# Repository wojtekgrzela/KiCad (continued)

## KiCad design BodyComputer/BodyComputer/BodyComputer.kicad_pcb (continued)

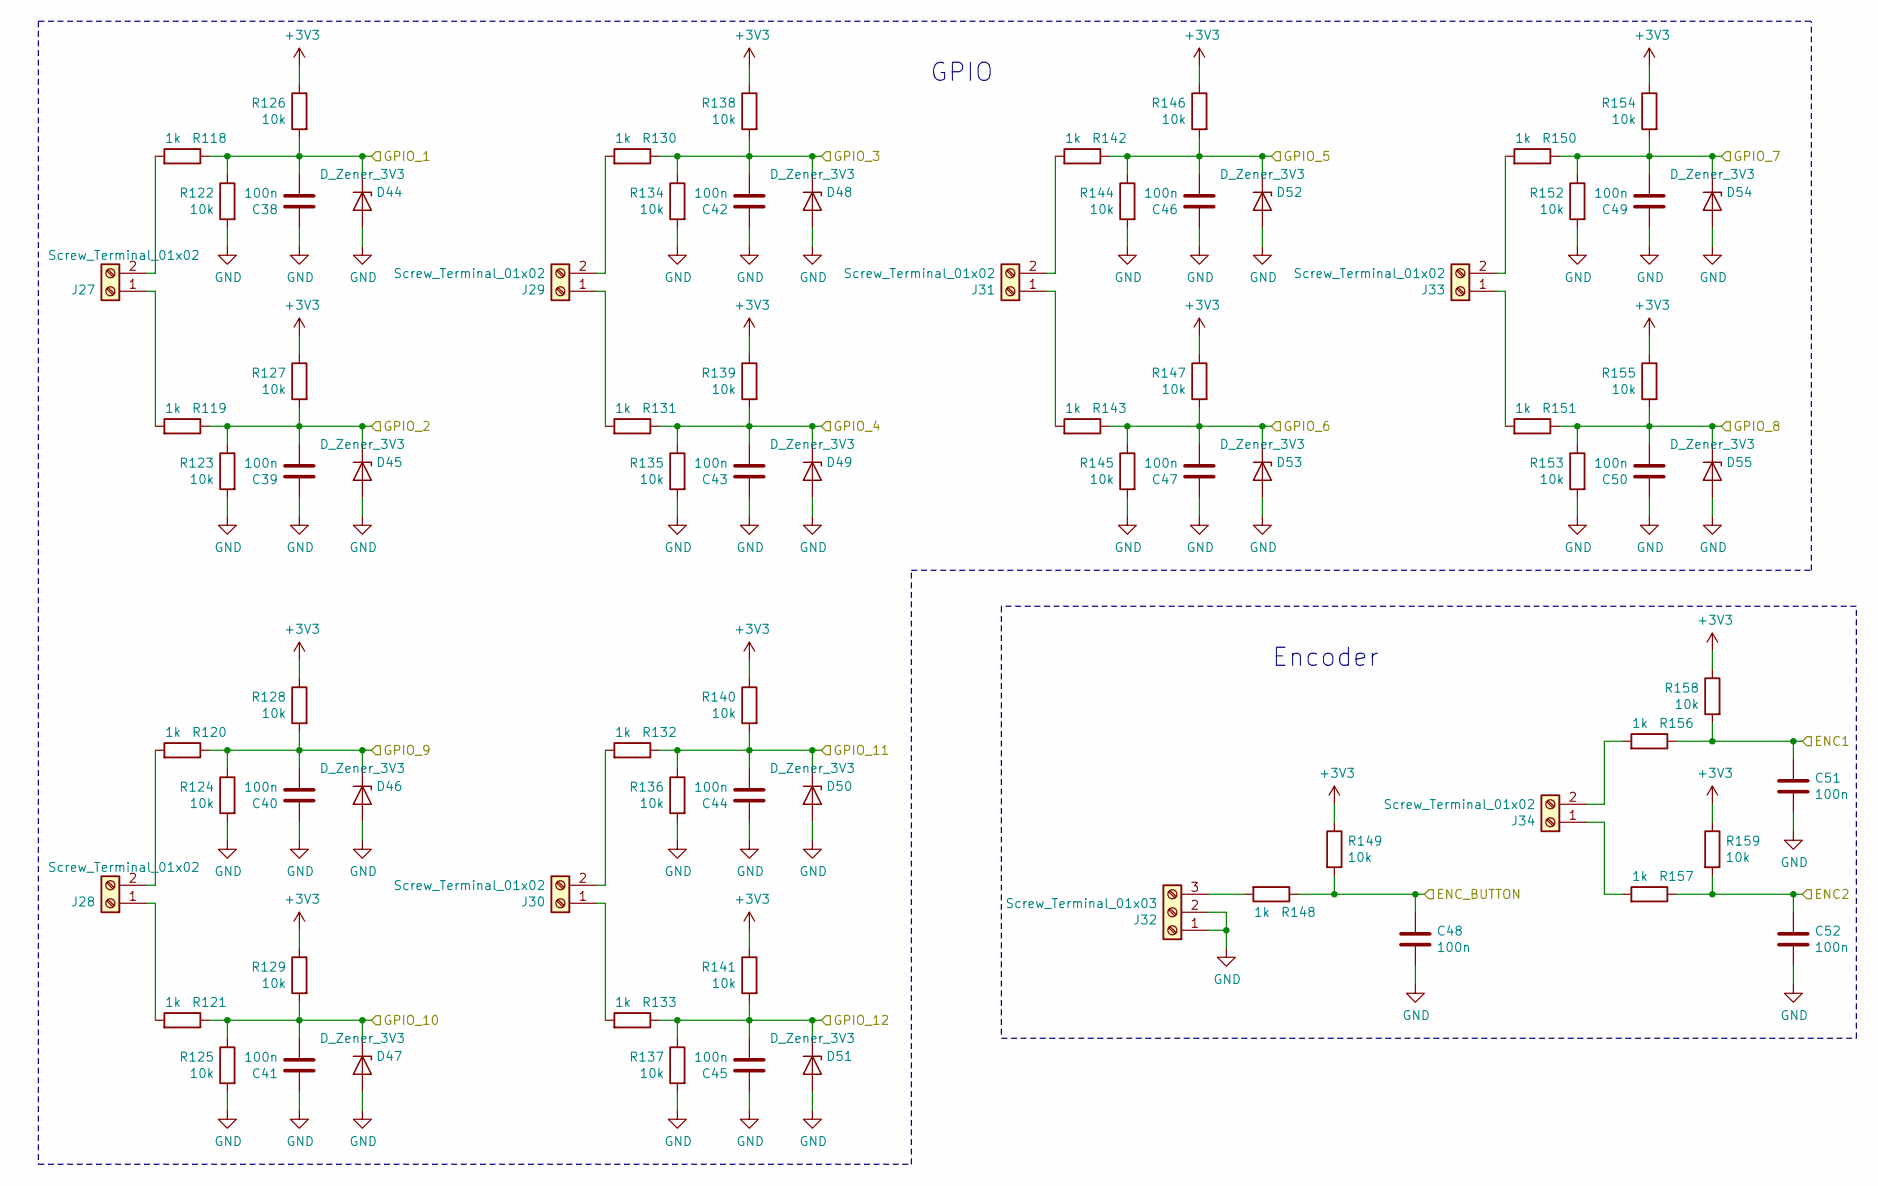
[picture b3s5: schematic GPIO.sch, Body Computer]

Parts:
C38, C39, C40, C41, C42, C43, C44, C45, C46, C47, C48, C49, C50, C51, C52: 100n; C_0603_1608Metric
D44, D45, D46, D47, D48, D49, D50, D51, D52, D53, D54, D55: D_Zener_3V3; D_SOD-323_HandSoldering
J27, J28, J29, J30, J31, J33, J34: Screw_Terminal_01x02; SHDR2W99P0X500_1X2_1000X760X1000P
J32: Screw_Terminal_01x03; SHDR3W95P0X500_1X3_1620X900X1280P
R118, R119, R120, R121, R130, R131, R132, R133, R142, R143, R148, R150, R151, R156, R157: 1k; R_0603_1608Metric
R122, R123, R124, R125, R126, R127, R128, R129, R134, R135, R136, R137, R138, R139, R140, R141, R144, R145, R146, R147, R149, R152, R153, R154, R155, R158, R159: 10k; R_0603_1608Metric

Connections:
+3V3: R126.1, R127.1, R128.1, R129.1, R138.1, R139.1, R140.1, R141.1, R146.1, R147.1, R149.1, R154.1, R155.1, R158.1, R159.1; also elsewhere on the board
/GPIO/ENC1: C51.1, R156.1, R158.2; also elsewhere on the board
/GPIO/ENC2: C52.1, R157.1, R159.2; also elsewhere on the board
/GPIO/ENC_BUTTON: C48.1, R148.1, R149.2; also elsewhere on the board
/GPIO/GPIO_1: C38.2, D44.1 (K), R118.1, R122.1, R126.2; also elsewhere on the board
/GPIO/GPIO_2: C39.2, D45.1 (K), R119.1, R123.1, R127.2; also elsewhere on the board
/GPIO/GPIO_3: C42.2, D48.1 (K), R130.1, R134.1, R138.2; also elsewhere on the board
/GPIO/GPIO_4: C43.2, D49.1 (K), R131.1, R135.1, R139.2; also elsewhere on the board
/GPIO/GPIO_5: C46.2, D52.1 (K), R142.1, R144.1, R146.2; also elsewhere on the board
/GPIO/GPIO_6: C47.2, D53.1 (K), R143.1, R145.1, R147.2; also elsewhere on the board
/GPIO/GPIO_7: C49.2, D54.1 (K), R150.1, R152.1, R154.2; also elsewhere on the board
/GPIO/GPIO_8: C50.2, D55.1 (K), R151.1, R153.1, R155.2; also elsewhere on the board
/GPIO/GPIO_9: C40.2, D46.1 (K), R120.1, R124.1, R128.2; also elsewhere on the board
/GPIO/GPIO_10: C41.2, D47.1 (K), R121.1, R125.1, R129.2; also elsewhere on the board
/GPIO/GPIO_11: C44.2, D50.1 (K), R132.1, R136.1, R140.2; also elsewhere on the board
/GPIO/GPIO_12: C45.2, D51.1 (K), R133.1, R137.1, R141.2; also elsewhere on the board
GND: C38.1, C39.1, C40.1, C41.1, C42.1, C43.1, C44.1, C45.1, C46.1, C47.1, C48.2, C49.1, C50.1, C51.2, C52.2, D44.2 (A), D45.2 (A), D46.2 (A), D47.2 (A), D48.2 (A), D49.2 (A), D50.2 (A), D51.2 (A), D52.2 (A), D53.2 (A), D54.2 (A), D55.2 (A), J32.1, J32.2, R122.2, R123.2, R124.2, R125.2, R134.2, R135.2, R136.2, R137.2, R144.2, R145.2, R152.2, R153.2; also elsewhere on the board
unnamed: J27.1, R119.2
unnamed: J27.2, R118.2
unnamed: J28.1, R121.2
unnamed: J28.2, R120.2
unnamed: J29.1, R131.2
unnamed: J29.2, R130.2
unnamed: J30.1, R133.2
unnamed: J30.2, R132.2
unnamed: J31.1, R143.2
unnamed: J31.2, R142.2
unnamed: J32.3, R148.2
unnamed: J33.1, R151.2
unnamed: J33.2, R150.2
unnamed: J34.1, R157.2
unnamed: J34.2, R156.2

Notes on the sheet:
GPIO
Encoder

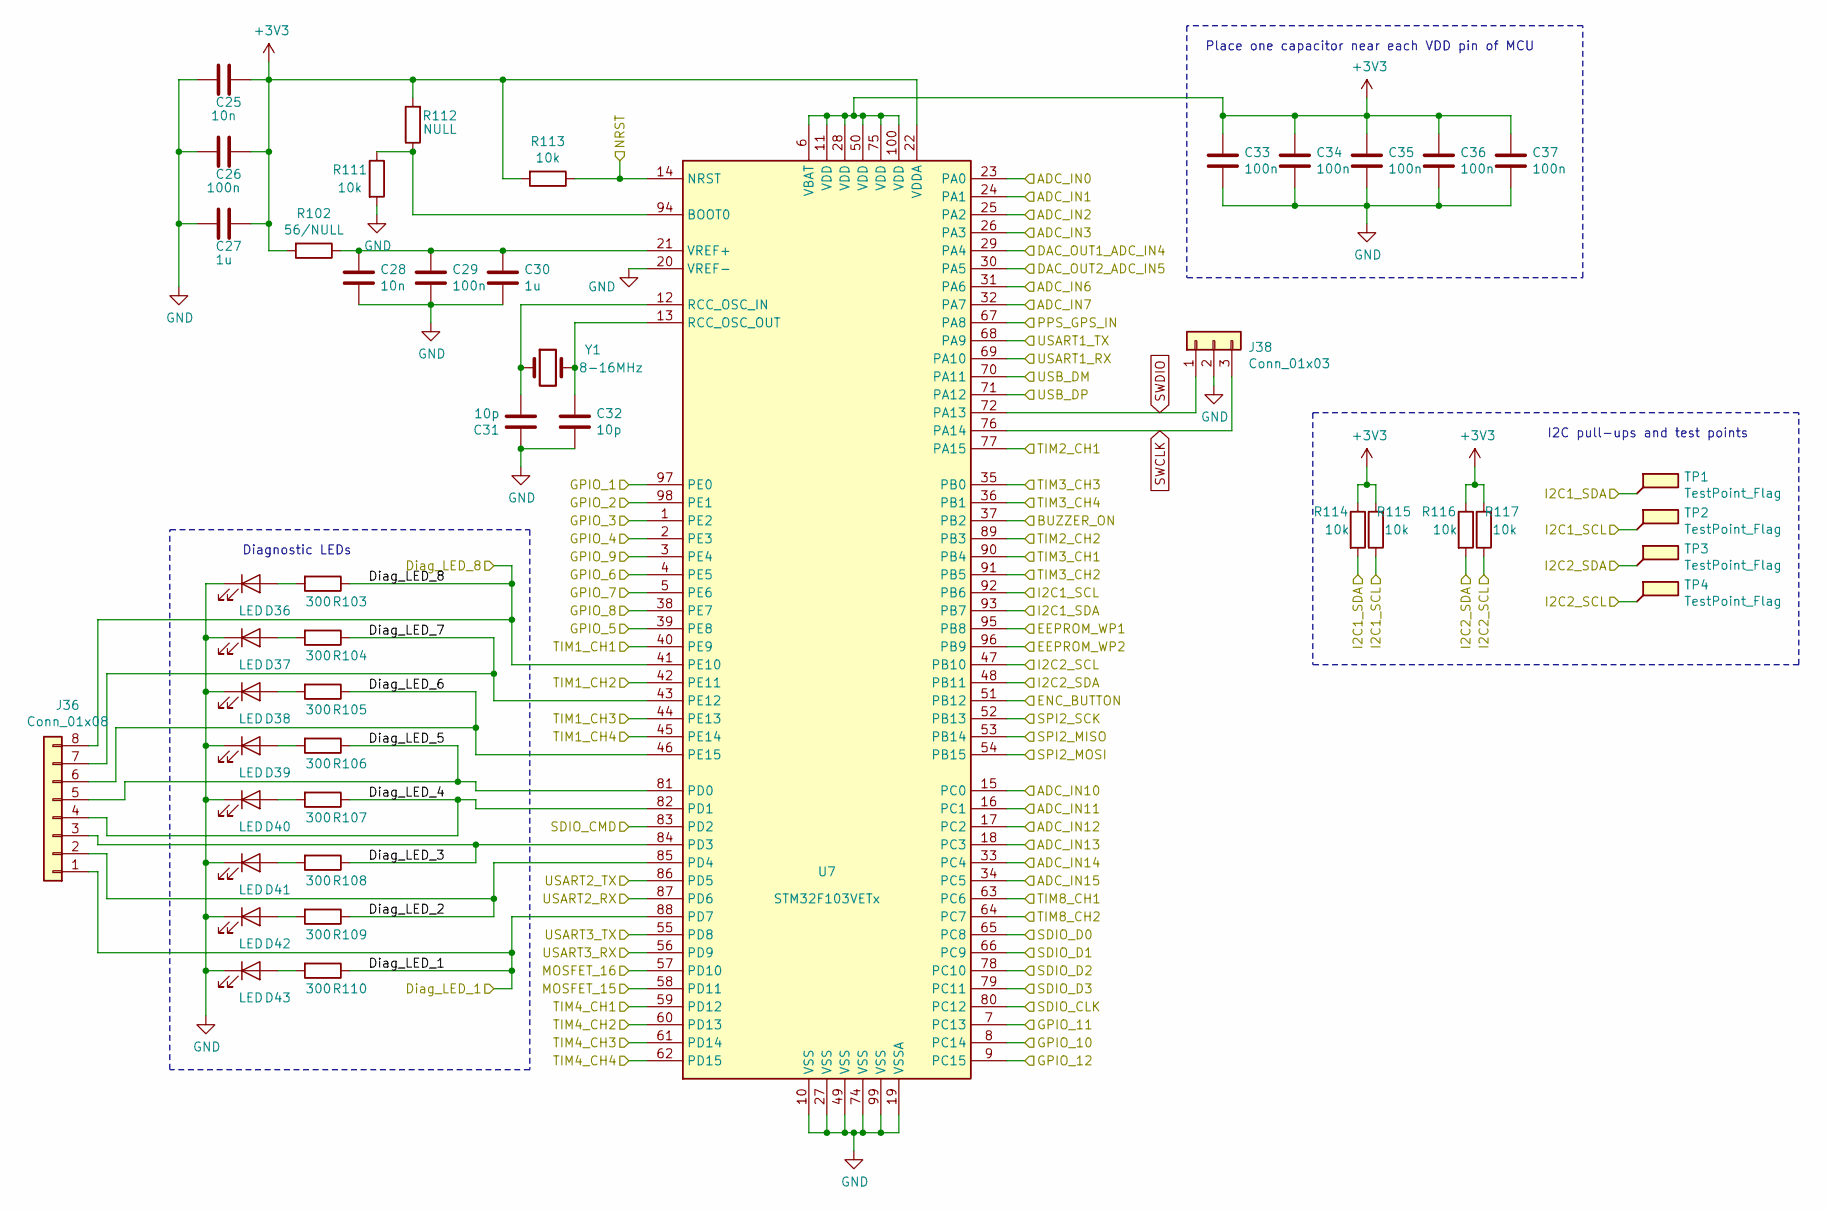
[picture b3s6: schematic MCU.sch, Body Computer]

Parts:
C25, C28: 10n; C_0603_1608Metric
C26, C29, C33, C34, C35, C36, C37: 100n; C_0603_1608Metric
C27, C30: 1u; C_0603_1608Metric
C31, C32: 10p; C_0603_1608Metric
D36, D37, D38, D39, D40, D41, D42, D43: LED; D_0603_1608Metric_Pad1.05x0.95mm_HandSolder
J36: Conn_01x08; PinHeader_1x08_P2.54mm_Vertical
J38: Conn_01x03; PinHeader_1x03_P2.54mm_Vertical
R102: 56/NULL; R_0603_1608Metric
R103, R104, R105, R106, R107, R108, R109, R110: 300; R_0603_1608Metric
R111, R113, R114, R115, R116, R117: 10k; R_0603_1608Metric
R112: NULL; R_0603_1608Metric
TP1, TP2, TP3, TP4: TestPoint_Flag; TestPoint_Pad_D1.0mm
U7: STM32F103VETx; LQFP-100_14x14mm_P0.5mm
Y1: 8-16MHz; Crystal_SMD_SeikoEpson_MA505-2Pin_12.7x5.1mm

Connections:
+3V3: C25.1, C26.1, C27.1, C33.1, C34.1, C35.1, C36.1, C37.1, R102.2, R112.2, R113.2, R114.1, R115.2, R116.1, R117.2, U7.6 (VBAT), U7.11 (VDD), U7.22 (VDDA), U7.28 (VDD), U7.50 (VDD), U7.75 (VDD), U7.100 (VDD); also elsewhere on the board
/GPIO/ENC1: U7.63 (PC6); also elsewhere on the board
/GPIO/ENC2: U7.64 (PC7); also elsewhere on the board
/GPIO/ENC_BUTTON: U7.51 (PB12); also elsewhere on the board
/GPIO/GPIO_1: U7.97 (PE0); also elsewhere on the board
/GPIO/GPIO_2: U7.98 (PE1); also elsewhere on the board
/GPIO/GPIO_3: U7.1 (PE2); also elsewhere on the board
/GPIO/GPIO_4: U7.2 (PE3); also elsewhere on the board
/GPIO/GPIO_5: U7.39 (PE8); also elsewhere on the board
/GPIO/GPIO_6: U7.4 (PE5); also elsewhere on the board
/GPIO/GPIO_7: U7.5 (PE6); also elsewhere on the board
/GPIO/GPIO_8: U7.38 (PE7); also elsewhere on the board
/GPIO/GPIO_9: U7.3 (PE4); also elsewhere on the board
/GPIO/GPIO_10: U7.8 (PC14); also elsewhere on the board
/GPIO/GPIO_11: U7.7 (PC13); also elsewhere on the board
/GPIO/GPIO_12: U7.9 (PC15); also elsewhere on the board
/Inputs_Outputs/ADC_1: U7.25 (PA2); also elsewhere on the board
/Inputs_Outputs/ADC_2: U7.26 (PA3); also elsewhere on the board
/Inputs_Outputs/ADC_3: U7.31 (PA6); also elsewhere on the board
/Inputs_Outputs/ADC_4: U7.32 (PA7); also elsewhere on the board
/Inputs_Outputs/ADC_5: U7.33 (PC4); also elsewhere on the board
/Inputs_Outputs/ADC_6: U7.34 (PC5); also elsewhere on the board
/Inputs_Outputs/ADC_7: U7.23 (PA0); also elsewhere on the board
/Inputs_Outputs/ADC_8: U7.24 (PA1); also elsewhere on the board
/Inputs_Outputs/AN_IN1_DAC1_INPUT: U7.29 (PA4); also elsewhere on the board
/Inputs_Outputs/AN_IN2_DAC2_INPUT: U7.30 (PA5); also elsewhere on the board
/Inputs_Outputs/MOSFET_OUT_1: U7.40 (PE9); also elsewhere on the board
/Inputs_Outputs/MOSFET_OUT_2: U7.42 (PE11); also elsewhere on the board
/Inputs_Outputs/MOSFET_OUT_3: U7.44 (PE13); also elsewhere on the board
/Inputs_Outputs/MOSFET_OUT_4: U7.45 (PE14); also elsewhere on the board
/Inputs_Outputs/MOSFET_OUT_5: U7.77 (PA15); also elsewhere on the board
/Inputs_Outputs/MOSFET_OUT_6: U7.89 (PB3); also elsewhere on the board
/Inputs_Outputs/MOSFET_OUT_7: U7.90 (PB4); also elsewhere on the board
/Inputs_Outputs/MOSFET_OUT_8: U7.91 (PB5); also elsewhere on the board
/Inputs_Outputs/MOSFET_OUT_9: U7.35 (PB0); also elsewhere on the board
/Inputs_Outputs/MOSFET_OUT_10: U7.36 (PB1); also elsewhere on the board
/Inputs_Outputs/MOSFET_OUT_11: U7.59 (PD12); also elsewhere on the board
/Inputs_Outputs/MOSFET_OUT_12: U7.60 (PD13); also elsewhere on the board
/Inputs_Outputs/MOSFET_OUT_13: U7.61 (PD14); also elsewhere on the board
/Inputs_Outputs/MOSFET_OUT_14: U7.62 (PD15); also elsewhere on the board
/MCU/ADC_IN10: U7.15 (PC0); also elsewhere on the board
/MCU/ADC_IN12: U7.17 (PC2); also elsewhere on the board
/MCU/ADC_IN13: U7.18 (PC3); also elsewhere on the board
/MCU/Diag_LED_1: J36.1, R110.1, U7.88 (PD7); also elsewhere on the board
/MCU/Diag_LED_2: J36.2, R109.1, U7.85 (PD4)
/MCU/Diag_LED_3: J36.3, R108.1, U7.84 (PD3)
/MCU/Diag_LED_4: J36.4, R107.1, U7.82 (PD1)
/MCU/Diag_LED_5: J36.5, R106.1, U7.81 (PD0)
/MCU/Diag_LED_6: J36.6, R105.1, U7.46 (PE15)
/MCU/Diag_LED_7: J36.7, R104.1, U7.43 (PE12)
/MCU/Diag_LED_8: J36.8, R103.1, U7.41 (PE10); also elsewhere on the board
/MCU/EEPROM_WP1: U7.95 (PB8); also elsewhere on the board
/MCU/EEPROM_WP2: U7.96 (PB9); also elsewhere on the board
/MCU/I2C2_SCL: R117.1, TP4.1, U7.47 (PB10); also elsewhere on the board
/MCU/I2C2_SDA: R116.2, TP3.1, U7.48 (PB11); also elsewhere on the board
/MCU/MOSFET_15: U7.58 (PD11); also elsewhere on the board
/MCU/MOSFET_16: U7.57 (PD10); also elsewhere on the board
/MCU/NRST: R113.1, U7.14 (NRST); also elsewhere on the board
/Memory/EEPROM_SCL: R115.1, TP2.1, U7.92 (PB6); also elsewhere on the board
/Memory/EEPROM_SDA: R114.2, TP1.1, U7.93 (PB7); also elsewhere on the board
/Memory/FLASH_DATA_0: U7.65 (PC8); also elsewhere on the board
/Memory/FLASH_DATA_1: U7.66 (PC9); also elsewhere on the board
/Memory/FLASH_DATA_2: U7.78 (PC10); also elsewhere on the board
/Memory/FLASH_DATA_3: U7.79 (PC11); also elsewhere on the board
/Memory/FLASH_DATA_CLK: U7.80 (PC12); also elsewhere on the board
/Memory/FLASH_DATA_CMD: U7.83 (PD2); also elsewhere on the board
/Peripherals/BUZZER: U7.37 (PB2); also elsewhere on the board
/Peripherals/MISO: U7.53 (PB14); also elsewhere on the board
/Peripherals/MOSI: U7.54 (PB15); also elsewhere on the board
/Peripherals/PPS_GPS: U7.67 (PA8); also elsewhere on the board
/Peripherals/RX: U7.56 (PD9); also elsewhere on the board
/Peripherals/RXD2_NODEMCU: U7.86 (PD5); also elsewhere on the board
/Peripherals/RX_GPS: U7.68 (PA9); also elsewhere on the board
/Peripherals/SCK: U7.52 (PB13); also elsewhere on the board
/Peripherals/TX: U7.55 (PD8); also elsewhere on the board
/Peripherals/TX2D_NODEMCU: U7.87 (PD6); also elsewhere on the board
/Peripherals/TX_GPS: U7.69 (PA10); also elsewhere on the board
/Peripherals/USB_DATA+: U7.71 (PA12); also elsewhere on the board
/Peripherals/USB_DATA-: U7.70 (PA11); also elsewhere on the board
/PowerSupply_and_BoardTemp/5V_MEASURE: U7.16 (PC1); also elsewhere on the board
GND: C25.2, C26.2, C27.2, C28.2, C29.2, C30.2, C31.1, C32.2, C33.2, C34.2, C35.2, C36.2, C37.2, D36.1 (K), D37.1 (K), D38.1 (K), D39.1 (K), D40.1 (K), D41.1 (K), D42.1 (K), D43.1 (K), J38.2, R111.2, U7.10 (VSS), U7.19 (VSSA), U7.20 (VREF-), U7.27 (VSS), U7.49 (VSS), U7.74 (VSS), U7.99 (VSS); also elsewhere on the board
unnamed: C28.1, C29.1, C30.1, R102.1, U7.21 (VREF+)
unnamed: C31.2, U7.12 (RCC_OSC_IN), Y1.1
unnamed: C32.1, U7.13 (RCC_OSC_OUT), Y1.2
unnamed: D36.2 (A), R103.2
unnamed: D37.2 (A), R104.2
unnamed: D38.2 (A), R105.2
unnamed: D39.2 (A), R106.2
unnamed: D40.2 (A), R107.2
unnamed: D41.2 (A), R108.2
unnamed: D42.2 (A), R109.2
unnamed: D43.2 (A), R110.2
unnamed: R111.1, R112.1, U7.94 (BOOT0)
SWCLK: J38.3, U7.76 (PA14)
SWDIO: J38.1, U7.72 (PA13)

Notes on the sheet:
Place one capacitor near each VDD pin of MCU
I2C pull-ups and test points
Diagnostic LEDs

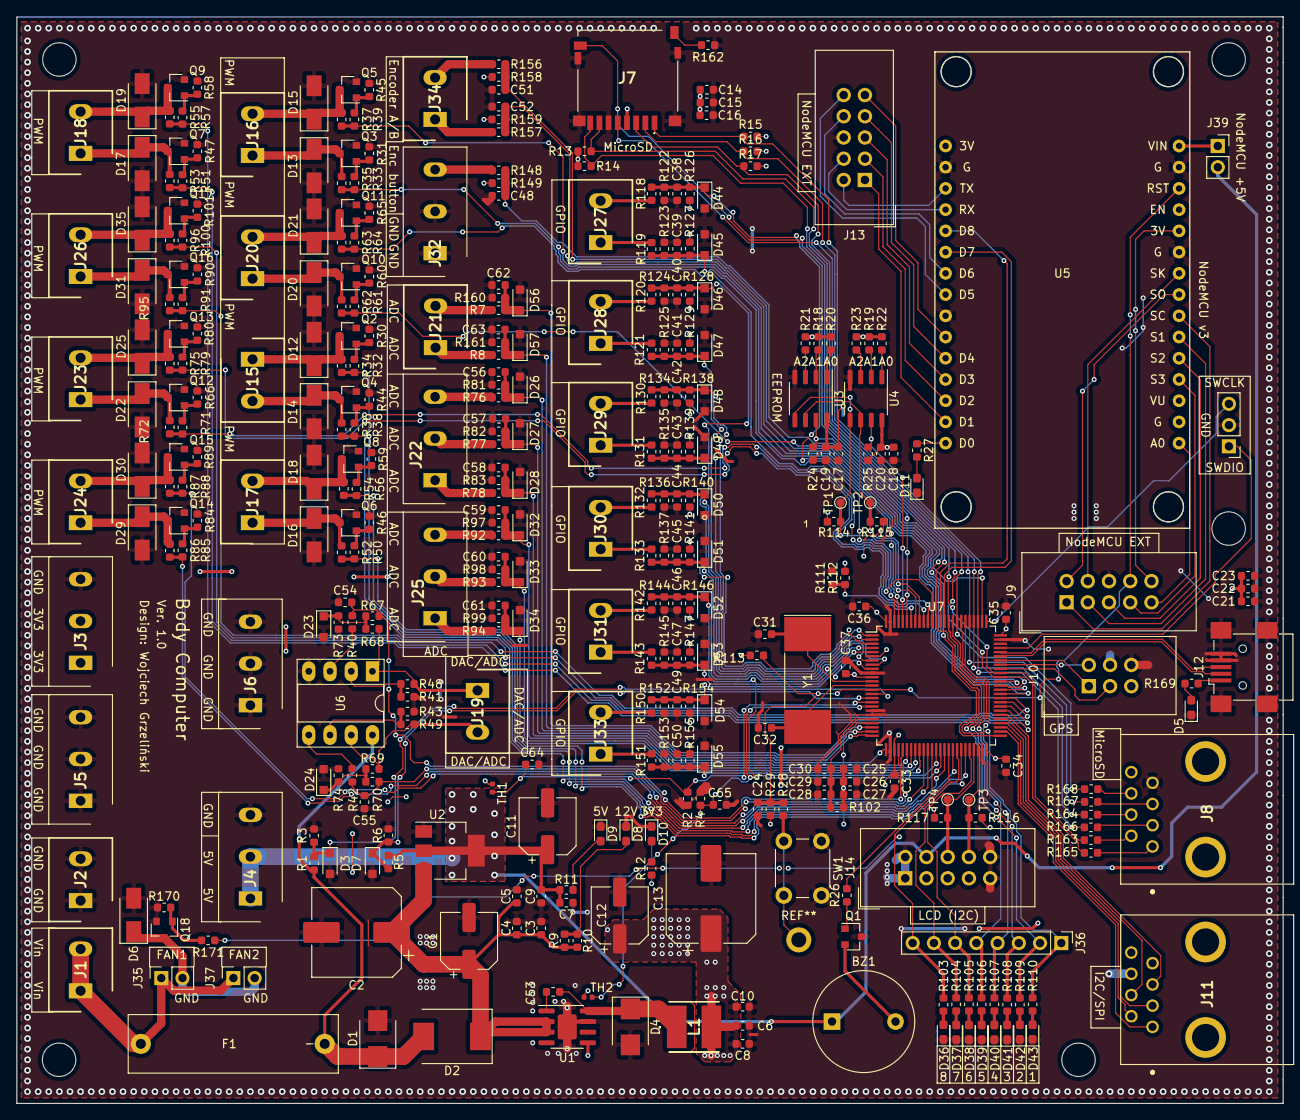
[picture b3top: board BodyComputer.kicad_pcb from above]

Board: 2 copper layers, 151.5 x 130.0 mm, 368 parts (0 on the bottom side), 207 nets.

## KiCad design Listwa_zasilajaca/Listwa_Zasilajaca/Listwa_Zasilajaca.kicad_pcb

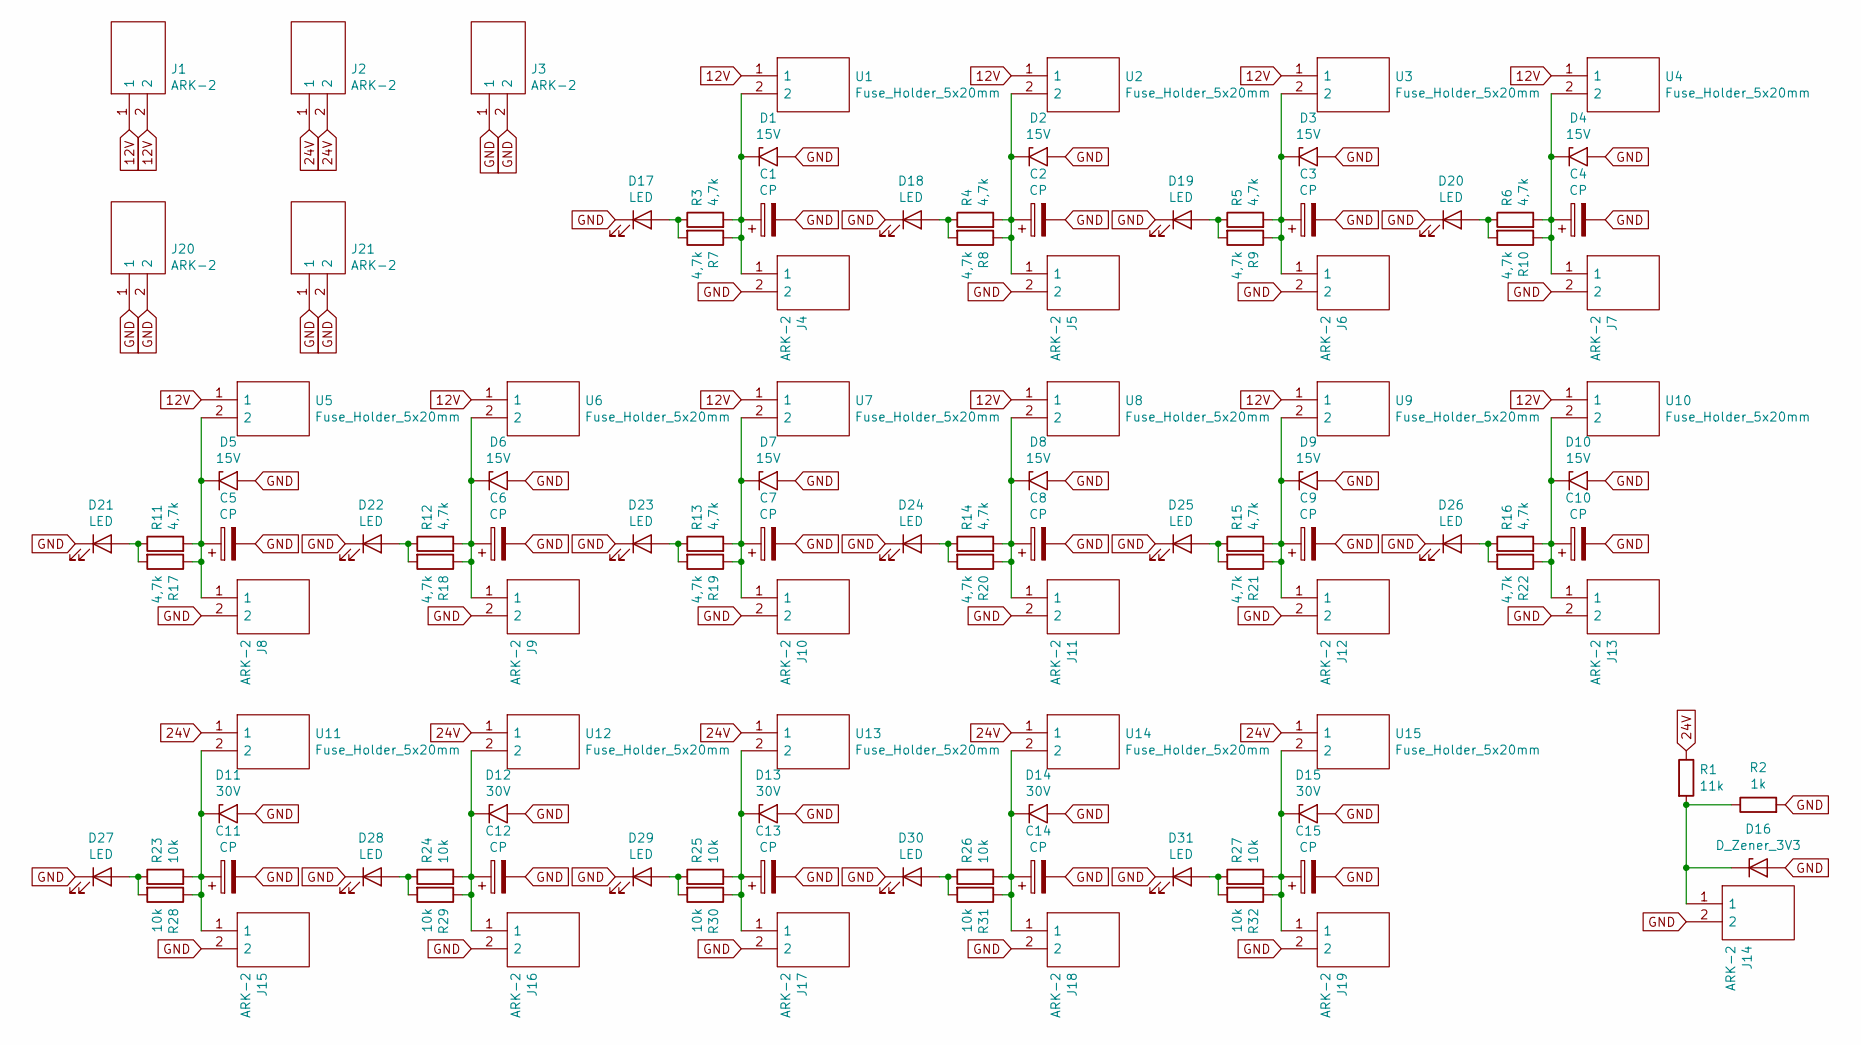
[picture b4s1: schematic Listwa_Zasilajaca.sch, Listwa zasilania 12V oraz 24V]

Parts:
C1, C2, C3, C4, C5, C6, C7, C8, C9, C10, C11, C12, C13, C14, C15: CP; CP_Radial_D5.0mm_P2.00mm
D1, D2, D3, D4, D5, D6, D7, D8, D9, D10: 15V; D_DO-201AE_P15.24mm_Horizontal
D11, D12, D13, D14, D15: 30V; D_DO-201AE_P15.24mm_Horizontal
D16: D_Zener_3V3; D_SOD-123
D17, D18, D19, D20, D21, D22, D23, D24, D25, D26, D27, D28, D29, D30, D31: LED; D_0603_1608Metric
J1, J2, J3, J4, J5, J6, J7, J8, J9, J10, J11, J12, J13, J14, J15, J16, J17, J18, J19, J20, J21: ARK-2; SHDR2W99P0X500_1X2_1000X760X1000P; Mouser Part Number 534-8718
R1: 11k; R_0603_1608Metric
R2: 1k; R_0603_1608Metric
R3, R4, R5, R6, R7, R8, R9, R10, R11, R12, R13, R14, R15, R16, R17, R18, R19, R20, R21, R22: 4,7k; R_0603_1608Metric
R23, R24, R25, R26, R27, R28, R29, R30, R31, R32: 10k; R_0603_1608Metric
U1, U2, U3, U4, U5, U6, U7, U8, U9, U10, U11, U12, U13, U14, U15: Fuse_Holder_5x20mm; 0PTF0078P; Mouser Part Number 576-0PTF0078P

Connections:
12V: J1.1, J1.2, U1.1, U2.1, U3.1, U4.1, U5.1, U6.1, U7.1, U8.1, U9.1, U10.1
24V: J2.1, J2.2, R1.1, U11.1, U12.1, U13.1, U14.1, U15.1
GND: C1.2, C2.2, C3.2, C4.2, C5.2, C6.2, C7.2, C8.2, C9.2, C10.2, C11.2, C12.2, C13.2, C14.2, C15.2, D1.2 (A2), D2.2 (A2), D3.2 (A2), D4.2 (A2), D5.2 (A2), D6.2 (A2), D7.2 (A2), D8.2 (A2), D9.2 (A2), D10.2 (A2), D11.2 (A2), D12.2 (A2), D13.2 (A2), D14.2 (A2), D15.2 (A2), D16.2 (A), D17.1 (K), D18.1 (K), D19.1 (K), D20.1 (K), D21.1 (K), D22.1 (K), D23.1 (K), D24.1 (K), D25.1 (K), D26.1 (K), D27.1 (K), D28.1 (K), D29.1 (K), D30.1 (K), D31.1 (K), J3.1, J3.2, J4.2, J5.2, J6.2, J7.2, J8.2, J9.2, J10.2, J11.2, J12.2, J13.2, J14.2, J15.2, J16.2, J17.2, J18.2, J19.2, J20.1, J20.2, J21.1, J21.2, R2.2
unnamed: C1.1, D1.1 (A1), J4.1, R3.2, R7.1, U1.2
unnamed: C2.1, D2.1 (A1), J5.1, R4.2, R8.1, U2.2
unnamed: C3.1, D3.1 (A1), J6.1, R5.2, R9.1, U3.2
unnamed: C4.1, D4.1 (A1), J7.1, R6.2, R10.1, U4.2
unnamed: C5.1, D5.1 (A1), J8.1, R11.2, R17.1, U5.2
unnamed: C6.1, D6.1 (A1), J9.1, R12.2, R18.1, U6.2
unnamed: C7.1, D7.1 (A1), J10.1, R13.2, R19.1, U7.2
unnamed: C8.1, D8.1 (A1), J11.1, R14.2, R20.1, U8.2
unnamed: C9.1, D9.1 (A1), J12.1, R15.2, R21.1, U9.2
unnamed: C10.1, D10.1 (A1), J13.1, R16.2, R22.1, U10.2
unnamed: C11.1, D11.1 (A1), J15.1, R23.2, R28.1, U11.2
unnamed: C12.1, D12.1 (A1), J16.1, R24.2, R29.1, U12.2
unnamed: C13.1, D13.1 (A1), J17.1, R25.2, R30.1, U13.2
unnamed: C14.1, D14.1 (A1), J18.1, R26.2, R31.1, U14.2
unnamed: C15.1, D15.1 (A1), J19.1, R27.2, R32.1, U15.2
unnamed: D16.1 (K), J14.1, R1.2, R2.1
unnamed: D17.2 (A), R3.1, R7.2
unnamed: D18.2 (A), R4.1, R8.2
unnamed: D19.2 (A), R5.1, R9.2
unnamed: D20.2 (A), R6.1, R10.2
unnamed: D21.2 (A), R11.1, R17.2
unnamed: D22.2 (A), R12.1, R18.2
unnamed: D23.2 (A), R13.1, R19.2
unnamed: D24.2 (A), R14.1, R20.2
unnamed: D25.2 (A), R15.1, R21.2
unnamed: D26.2 (A), R16.1, R22.2
unnamed: D27.2 (A), R23.1, R28.2
unnamed: D28.2 (A), R24.1, R29.2
unnamed: D29.2 (A), R25.1, R30.2
unnamed: D30.2 (A), R26.1, R31.2
unnamed: D31.2 (A), R27.1, R32.2

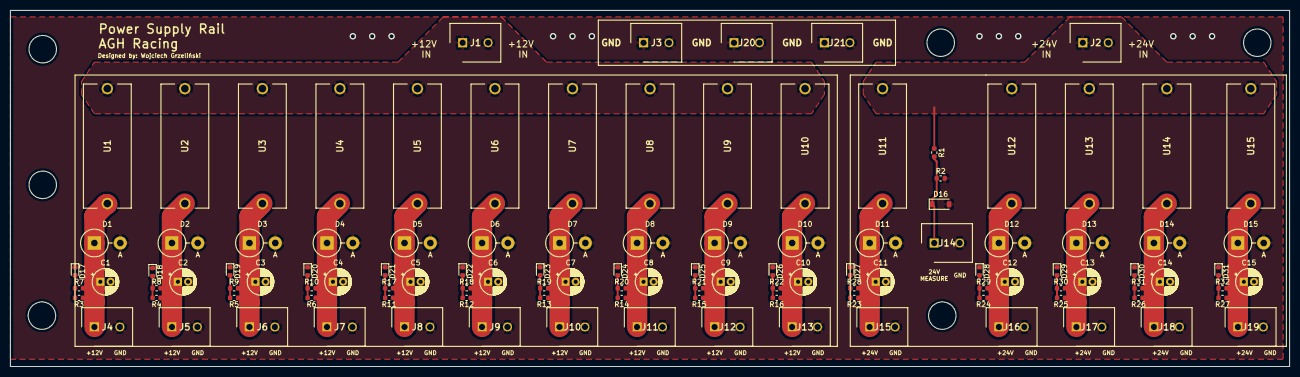
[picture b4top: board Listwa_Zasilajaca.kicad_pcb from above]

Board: 2 copper layers, 251.5 x 70.0 mm, 114 parts (0 on the bottom side), 34 nets.

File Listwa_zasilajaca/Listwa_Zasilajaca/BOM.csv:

Id,Oznaczenie,Obudowa,Ilość,Oznaczenie,Dostawca i numer artykułu
1,"J21,J20,J19,J18,J17,J16,J15,J14,J13,J12,J11,J10,J9,J8,J7,J6,J5,J4,J3,J2,J1",SHDR2W99P0X500_1X2_1000X760X1000P,21,ARK-2,https://www.tme.eu/pl/details/tb-5.0-p-2p-11/listwy-zaciskow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
2,"D15,D14,D13,D12,D11",D_DO-201_P5.08mm_Vertical_AnodeUp,5,30V,https://www.tme.eu/pl/details/1.5ke30a/diody-transil-tht-jed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
3,"D10,D9,D8,D7,D6,D5,D4,D3,D2,D1",D_DO-201_P5.08mm_Vertical_AnodeUp,10,15V,https://www.tme.eu/pl/details/1.5ke15a/diody-transil-tht-jed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
4,"U15,U14,U13,U12,U11,U10,U9,U8,U7,U6,U5,U4,U3,U2,U1",0PTF0078P,15,Fuse_Holder_5x20mm,https://www.tme.eu/pl/details/zhl78/gniazda-bezpiecznikowe-p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
5,R2,R_0603_1608Metric,1,1k,https://www.tme.eu/pl/details/wf06p-1k-5%25/rezystory-smd-06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
6,R1,R_0603_1608Metric,1,11k,https://www.tme.eu/pl/details/smd0603-11k/rezystory-smd-0603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
7,D16,D_SOD-123,1,D_Zener_3V3,https://www.tme.eu/pl/details/bzt52c3v3-7-f/diody-zenera-smd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
8,"C15,C14,C13,C12,C11,C10,C9,C8,C7,C6,C5,C4,C3,C2,C1",CP_Radial_D5.0mm_P2.00mm,15,CP,https://www.tme.eu/pl/details/pf1v330mnn0511u/kondensatory-e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
9,"R32,R31,R30,R29,R28,R27,R26,R25,R24,R23",R_0603_1608Metric,10,10k,https://www.tme.eu/pl/details/smd0603-10k/rezystory-smd-0603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 
10,"R22,R21,R20,R19,R18,R17,R16,R15,R14,R13,R12,R11,R10,R9,R8,R7,R6,R5,R4,R3",R_0603_1608Metric,20,"4,7k",https://www.tme.eu/pl/details/wf06p-4k7-5%25/rezystory-smd-0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 
11,"D31,D30,D29,D28,D27,D26,D25,D24,D23,D22,D21,D20,D19,D18,D17",D_0603_1608Metric,15,LED,https://www.tme.eu/pl/details/ll-s194pvc-v1-2b/diody-led-smd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

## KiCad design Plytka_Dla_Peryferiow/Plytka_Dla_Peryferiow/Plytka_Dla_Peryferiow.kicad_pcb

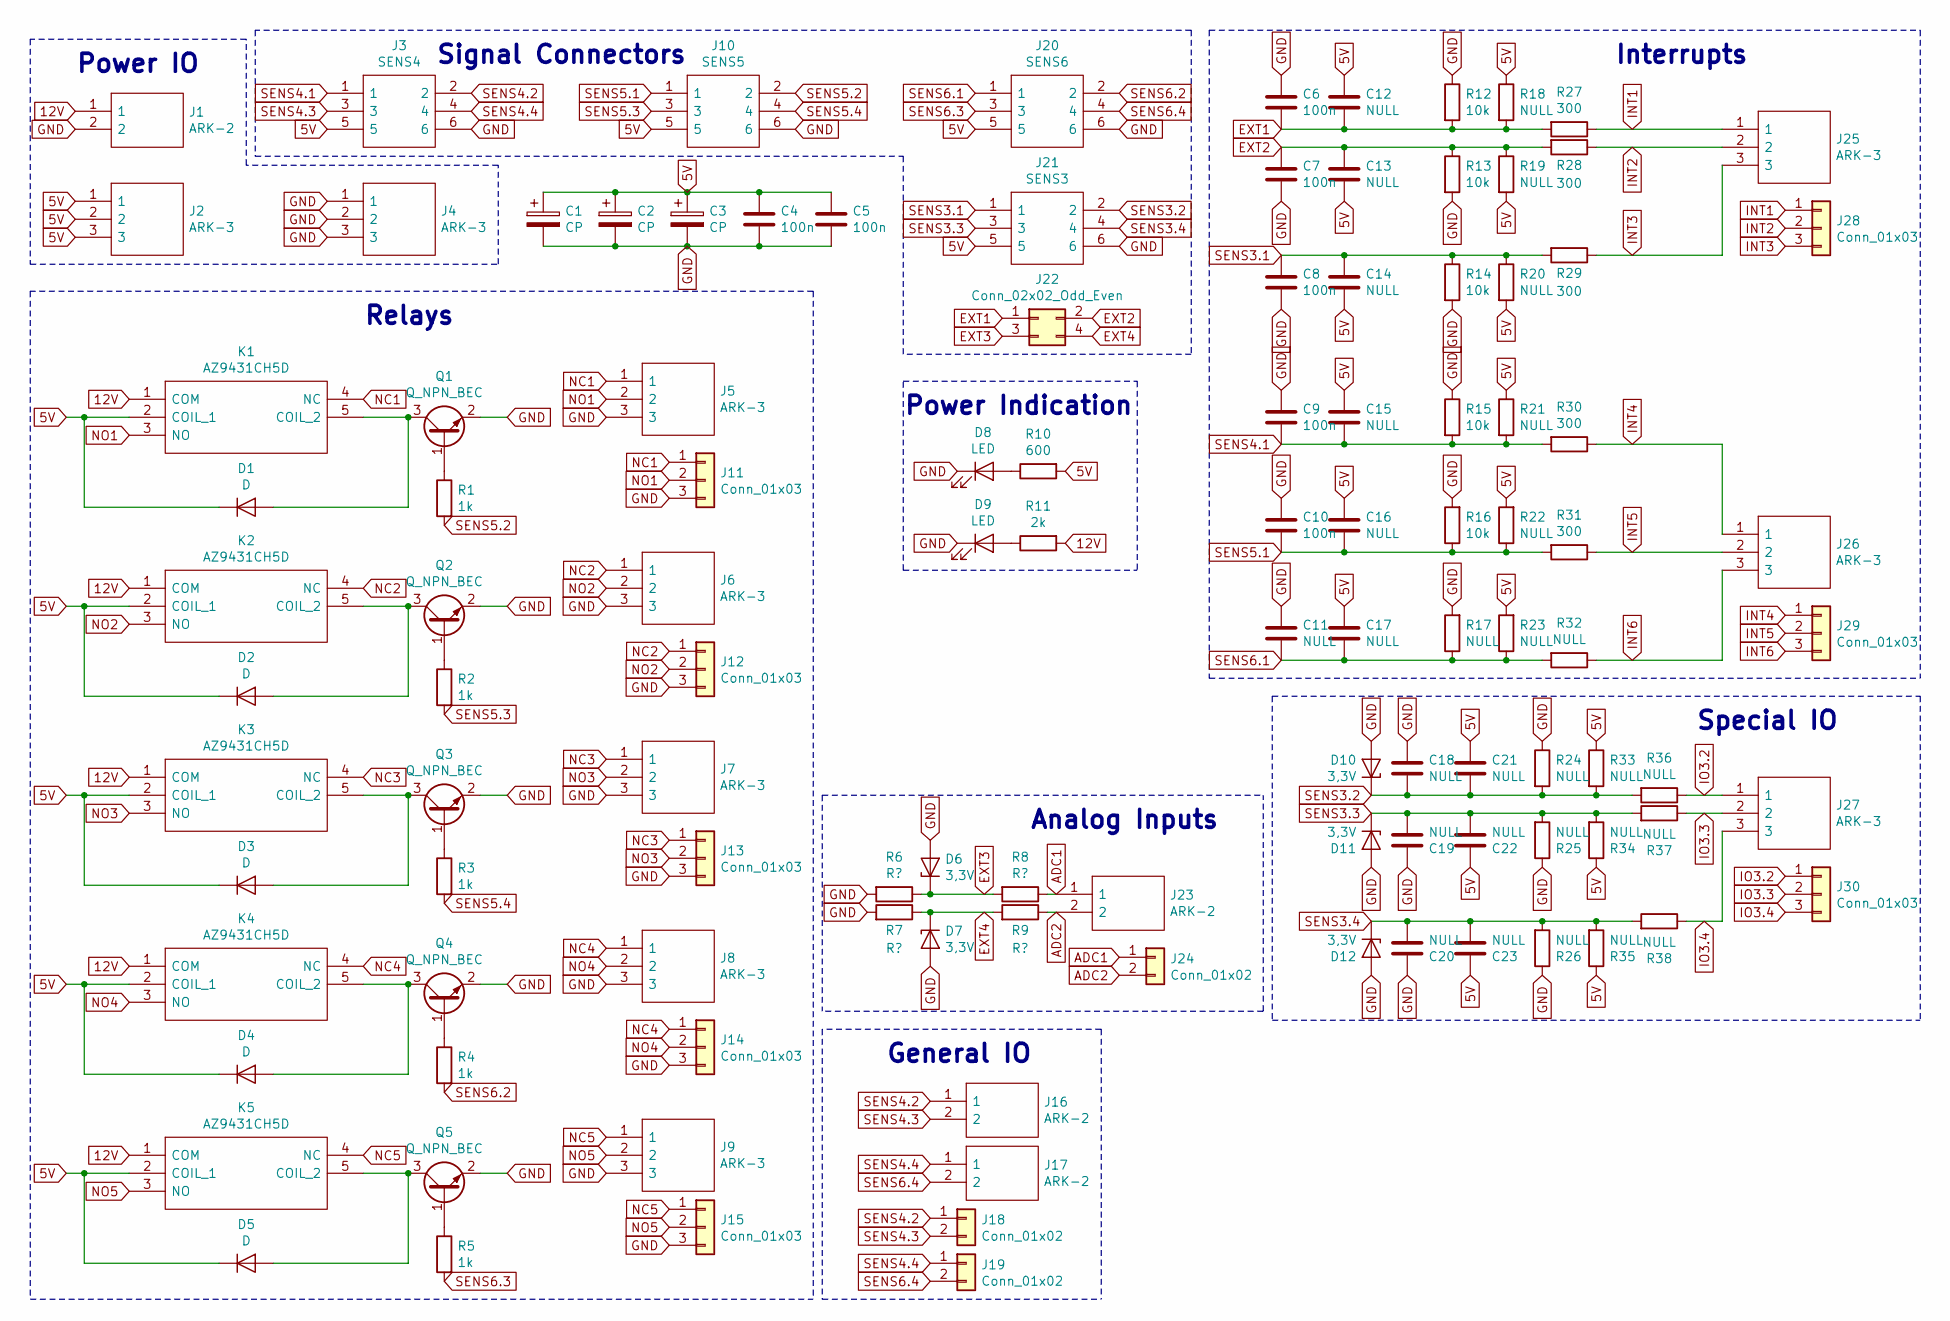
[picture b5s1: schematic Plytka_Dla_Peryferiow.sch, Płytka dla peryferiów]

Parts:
C1, C2, C3: CP; CP_Radial_D5.0mm_P2.00mm
C4, C5, C6, C7, C8, C9, C10: 100n; C_0603_1608Metric
C11, C12, C13, C14, C15, C16, C17, C18, C19, C20, C21, C22, C23: NULL; C_0603_1608Metric
D1, D2, D3, D4, D5: D; D_SOD-523
D6, D7, D10, D11, D12: 3,3V; D_SOD-123
D8, D9: LED; D_0603_1608Metric
J1, J16, J17, J23: ARK-2; SHDR2W99P0X500_1X2_1000X760X1000P; Mouser Part Number 534-8718
J2, J4, J5, J6, J7, J8, J9, J25, J26, J27: ARK-3; 8719; Mouser Part Number 534-8719
J3: SENS4; HDRV6W64P254X254_2X3_1524X895X915P; Mouser2 Part Number N/A
J10: SENS5; HDRV6W64P254X254_2X3_1524X895X915P; Mouser2 Part Number N/A
J11, J12, J13, J14, J15, J28, J29, J30: Conn_01x03; PinHeader_1x03_P2.54mm_Vertical
J18, J19, J24: Conn_01x02; PinHeader_1x02_P2.54mm_Vertical
J20: SENS6; HDRV6W64P254X254_2X3_1524X895X915P; Mouser2 Part Number N/A
J21: SENS3; HDRV6W64P254X254_2X3_1524X895X915P; Mouser2 Part Number N/A
J22: Conn_02x02_Odd_Even; PinHeader_2x02_P2.54mm_Vertical
K1, K2, K3, K4, K5: AZ9431CH5D; AZ943; Manufacturer_Part_Number AZ943–1CH–5D
Q1, Q2, Q3, Q4, Q5: Q_NPN_BEC; SOT-23
R1, R2, R3, R4, R5: 1k; R_0603_1608Metric
R6, R7, R8, R9: R?; R_0603_1608Metric
R10: 600; R_0603_1608Metric
R11: 2k; R_0603_1608Metric
R12, R13, R14, R15, R16: 10k; R_0603_1608Metric
R17, R18, R19, R20, R21, R22, R23, R24, R25, R26, R32, R33, R34, R35, R36, R37, R38: NULL; R_0603_1608Metric
R27, R28, R29, R30, R31: 300; R_0603_1608Metric

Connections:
5V: C1.1, C2.1, C3.1, C4.2, C5.2, C12.2, C13.1, C14.1, C15.2, C16.1, C17.1, C21.2, C22.2, C23.2, D1.1 (K), D2.1 (K), D3.1 (K), D4.1 (K), D5.1 (K), J2.1, J2.2, J2.3, J3.5, J10.5, J20.5, J21.5, K1.2 (COIL_1), K2.2 (COIL_1), K3.2 (COIL_1), K4.2 (COIL_1), K5.2 (COIL_1), R10.2, R18.1, R19.2, R20.2, R21.1, R22.2, R23.2, R33.1, R34.1, R35.1
12V: J1.1, K1.1 (COM), K2.1 (COM), K3.1 (COM), K4.1 (COM), K5.1 (COM), R11.2
ADC1: J23.1, J24.1, R8.1
ADC2: J23.2, J24.2, R9.1
EXT1: C6.1, C12.1, J22.1, R12.2, R18.2, R27.2
EXT2: C7.2, C13.2, J22.2, R13.1, R19.1, R28.2
EXT3: D6.1 (K), J22.3, R6.1, R8.2
EXT4: D7.1 (K), J22.4, R7.1, R9.2
GND: C1.2, C2.2, C3.2, C4.1, C5.1, C6.2, C7.1, C8.1, C9.2, C10.1, C11.1, C18.2, C19.2, C20.2, D6.2 (A), D7.2 (A), D8.1 (K), D9.1 (K), D10.2 (A), D11.2 (A), D12.2 (A), J1.2, J3.6, J4.1, J4.2, J4.3, J5.3, J6.3, J7.3, J8.3, J9.3, J10.6, J11.3, J12.3, J13.3, J14.3, J15.3, J20.6, J21.6, Q1.2 (E), Q2.2 (E), Q3.2 (E), Q4.2 (E), Q5.2 (E), R6.2, R7.2, R12.1, R13.2, R14.2, R15.1, R16.2, R17.2, R24.1, R25.1, R26.1
INT1: J25.1, J28.1, R27.1
INT2: J25.2, J28.2, R28.1
INT3: J25.3, J28.3, R29.1
INT4: J26.1, J29.1, R30.1
INT5: J26.2, J29.2, R31.1
INT6: J26.3, J29.3, R32.1
IO3.2: J27.1, J30.1, R36.1
IO3.3: J27.2, J30.2, R37.1
IO3.4: J27.3, J30.3, R38.1
NC1: J5.1, J11.1, K1.4 (NC)
NC2: J6.1, J12.1, K2.4 (NC)
NC3: J7.1, J13.1, K3.4 (NC)
NC4: J8.1, J14.1, K4.4 (NC)
NC5: J9.1, J15.1, K5.4 (NC)
NO1: J5.2, J11.2, K1.3 (NO)
NO2: J6.2, J12.2, K2.3 (NO)
NO3: J7.2, J13.2, K3.3 (NO)
NO4: J8.2, J14.2, K4.3 (NO)
NO5: J9.2, J15.2, K5.3 (NO)
unnamed: D1.2 (A), K1.5 (COIL_2), Q1.3 (C)
unnamed: D2.2 (A), K2.5 (COIL_2), Q2.3 (C)
unnamed: D3.2 (A), K3.5 (COIL_2), Q3.3 (C)
unnamed: D4.2 (A), K4.5 (COIL_2), Q4.3 (C)
unnamed: D5.2 (A), K5.5 (COIL_2), Q5.3 (C)
unnamed: D8.2 (A), R10.1
unnamed: D9.2 (A), R11.1
unnamed: Q1.1 (B), R1.1
unnamed: Q2.1 (B), R2.1
unnamed: Q3.1 (B), R3.1
unnamed: Q4.1 (B), R4.1
unnamed: Q5.1 (B), R5.1
SENS3.1: C8.2, C14.2, J21.1, R14.1, R20.1, R29.2
SENS3.2: C18.1, C21.1, D10.1 (K), J21.2, R24.2, R33.2, R36.2
SENS3.3: C19.1, C22.1, D11.1 (K), J21.3, R25.2, R34.2, R37.2
SENS3.4: C20.1, C23.1, D12.1 (K), J21.4, R26.2, R35.2, R38.2
SENS4.1: C9.1, C15.1, J3.1, R15.2, R21.2, R30.2
SENS4.2: J3.2, J16.1, J18.1
SENS4.3: J3.3, J16.2, J18.2
SENS4.4: J3.4, J17.1, J19.1
SENS5.1: C10.2, C16.2, J10.1, R16.1, R22.1, R31.2
SENS5.2: J10.2, R1.2
SENS5.3: J10.3, R2.2
SENS5.4: J10.4, R3.2
SENS6.1: C11.2, C17.2, J20.1, R17.1, R23.1, R32.2
SENS6.2: J20.2, R4.2
SENS6.3: J20.3, R5.2
SENS6.4: J17.2, J19.2, J20.4

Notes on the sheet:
Relays
Interrupts
Analog Inputs
General IO
Power Indication
Signal Connectors
Power IO
Special IO
